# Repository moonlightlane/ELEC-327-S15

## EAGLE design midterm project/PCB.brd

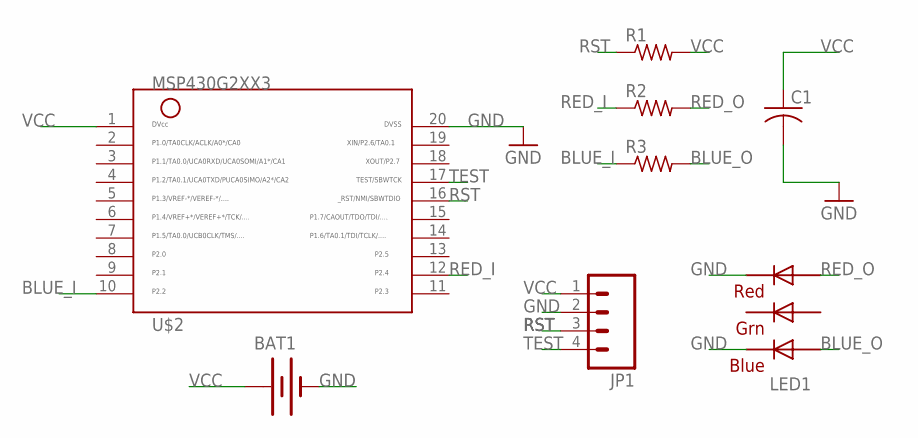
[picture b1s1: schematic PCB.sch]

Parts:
BAT1: BATTERYBU2032SM; BU2032SM
C1: C-USC1206; C1206
JP1: M04LOCK; 1X04_LOCK
LED1: RGBLED5050
R1, R2, R3: R-US_R1206; R1206
U$2: MSP430G2XX3TSSOP; PW20

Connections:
BLUE_I: R3.1, U$2.10
BLUE_O: LED1.3 (BLUE_A), R3.2
GND: BAT1.P$2 (-), C1.2, JP1.2, LED1.4 (BLUE_C), LED1.5 (RED_C), U$2.20
RED_I: R2.1, U$2.12
RED_O: LED1.2 (RED_A), R2.2
RST: JP1.3, R1.1, U$2.16
TEST: JP1.4, U$2.17
VCC: BAT1.P$1 (+), C1.1, JP1.1, R1.2, U$2.1

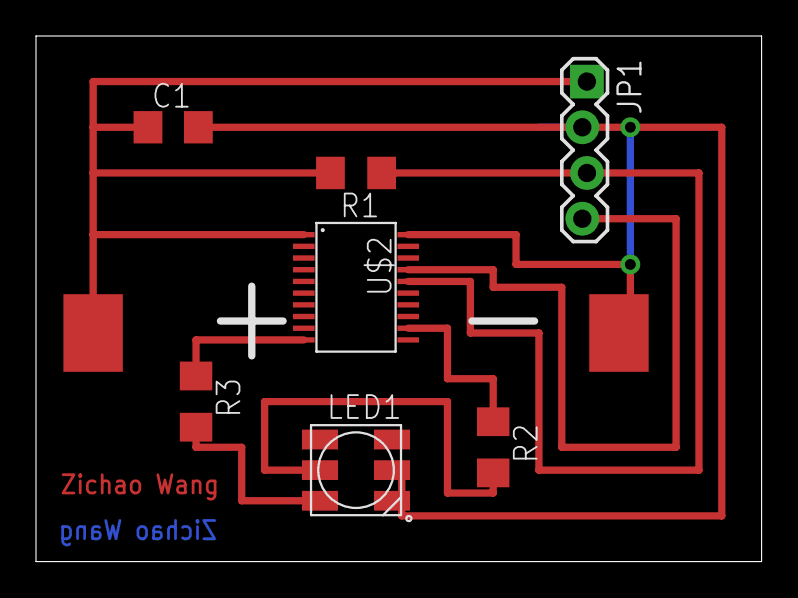
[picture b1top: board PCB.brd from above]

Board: 2 copper layers, 40.3 x 29.2 mm, 8 parts (0 on the bottom side), 8 nets.

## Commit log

2015-02-04 ELEC 327 Spring 15 Lab01
2015-02-04 ELEC 327 Spring 15 Lab02
2015-02-09 added lab 02 report
2015-02-11 added lab 3 code and updated lab 3 report
2015-02-12 added lab 03 code files
2015-02-13 updated lab03 code and report
2015-02-18 added pseudorandom number generator
2015-02-22 modified rand function
2015-03-30 added part 3 code
2015-03-30 update reports, midterm projects, etc
2015-03-30 lab 6 fixed led and buzzer change with correct pattern
2015-03-31 fixed watchdog timer interrupt routine
2015-03-31 added comments
2015-03-31 fixed everything. added re-programming mode
2015-04-14 added lab07 code

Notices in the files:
parts and their libraries:
SparkFun: Licensing: CC v3.0 Share-Alike You are welcome to use this library for commercial purposes.
